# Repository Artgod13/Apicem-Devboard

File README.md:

# Description
The Apicem Devboard is a Devboard designed by me for Hack Club. Currently it uses a RP2040 MCU, USB-C Power, 16 Mb Flash Storage, Reset Button, Power Indication LED, and a Neo Pixel Status LED. The board was designed to handle 0.6 amps of power. All of these features were added with what is essential in a board in mind. This board was designed to be like a Pi-Pico but way beefier and look cooler. In theory it should be exactly the same dimensions as a Pi-Pico and it uses the same MCu as the Pi-Pico. This board is named "Apicem" as that's latin for "vertex" or "peak" showing how this board is the peak of it's kind.

## Schematic

## PCB

## 3D Images

## My Documented Journey
See [My Journal](./JOURNAL.md)

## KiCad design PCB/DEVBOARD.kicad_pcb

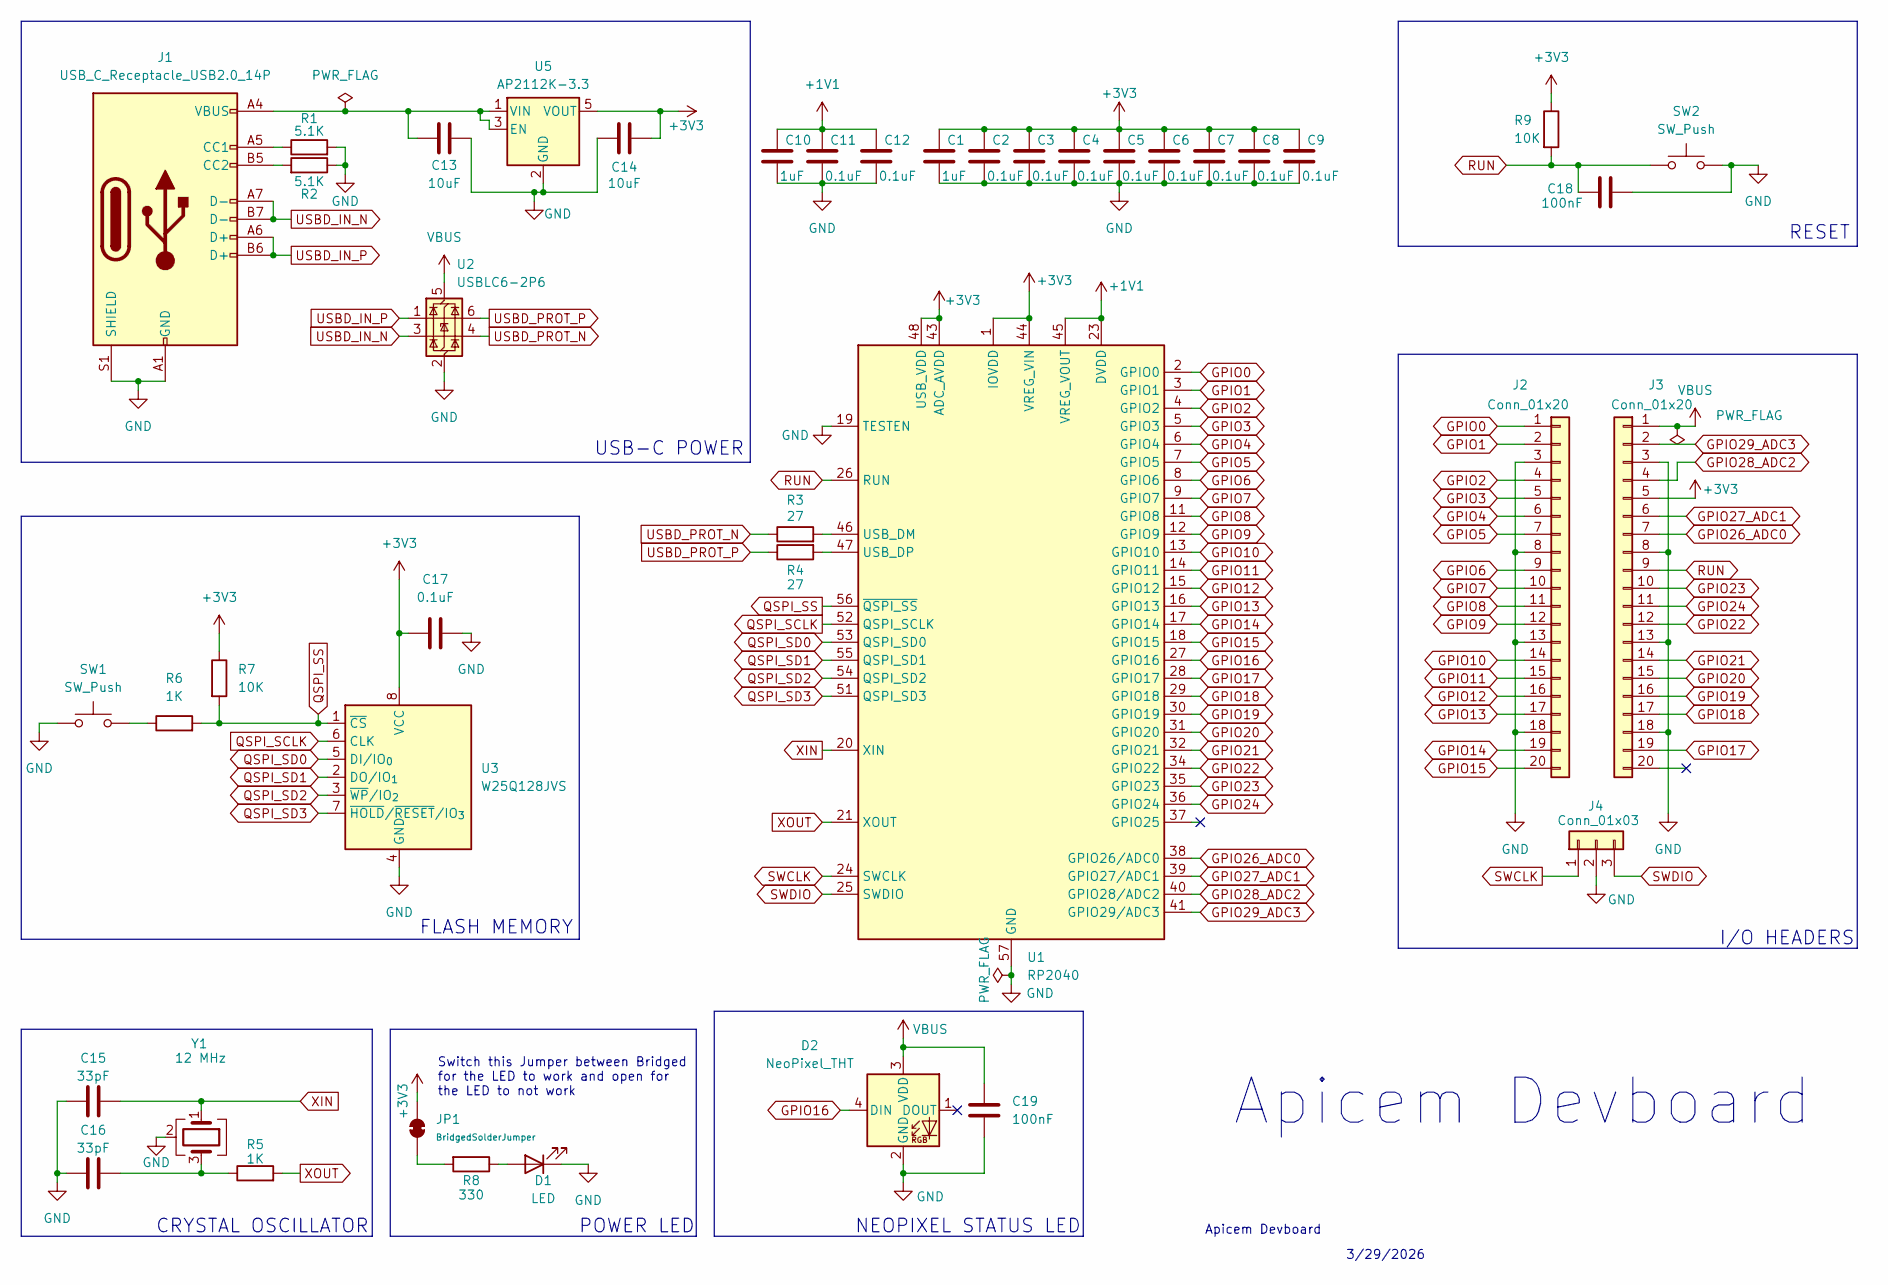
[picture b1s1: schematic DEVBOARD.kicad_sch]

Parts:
C1, C10: 1uF; C_0402_1005Metric
C2, C3, C4, C5, C6, C7, C8, C9, C11, C12, C17: 0.1uF; C_0402_1005Metric
C13, C14: 10uF; C_0603_1608Metric
C15, C16: 33pF; C_0402_1005Metric
C18, C19: 100nF; C_0402_1005Metric
D1: LED; LED_0603_1608Metric
D2: NeoPixel_THT; LED_SK6812MINI_PLCC4_3.5x3.5mm_P1.75mm
J1: USB_C_Receptacle_USB2.0_14P; USB_C_Receptacle_HRO_TYPE-C-31-M-12
J2, J3: Conn_01x20; PinHeader_1x20_P2.54mm_Vertical
J4: Conn_01x03; PinHeader_1x03_P2.54mm_Vertical
JP1: BridgedSolderJumper; SolderJumper-2_P1.3mm_Open_RoundedPad1.0x1.5mm
R1, R2: 5.1K; R_0402_1005Metric
R3, R4: 27; R_0402_1005Metric
R5, R6: 1K; R_0402_1005Metric
R7, R9: 10K; R_0402_1005Metric
R8: 330; R_0603_1608Metric
SW1, SW2: SW_Push; SW_Push_SPST_NO_Alps_SKRK
U1: RP2040; QFN-56-1EP_7x7mm_P0.4mm_EP3.2x3.2mm
U2: USBLC6-2P6; SOT-666
U3: W25Q128JVS; SOIC-8_5.3x5.3mm_P1.27mm
U5: AP2112K-3.3; SOT-23-5
Y1: 12 MHz; Crystal_SMD_3225-4Pin_3.2x2.5mm

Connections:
+1V1: C10.1, C11.1, C12.1, U1.23 (DVDD), U1.45 (VREG_VOUT), U1.50 (DVDD)
+3V3: C1.1, C2.1, C3.1, C4.1, C5.1, C6.1, C7.1, C8.1, C9.1, C14.2, C17.1, J3.5, JP1.2 (B), R7.1, R9.1, U1.1 (IOVDD), U1.10 (IOVDD), U1.22 (IOVDD), U1.33 (IOVDD), U1.42 (IOVDD), U1.43 (ADC_AVDD), U1.44 (VREG_VIN), U1.48 (USB_VDD), U1.49 (IOVDD), U3.8 (VCC), U5.5 (VOUT)
GND: C1.2, C2.2, C3.2, C4.2, C5.2, C6.2, C7.2, C8.2, C9.2, C10.2, C11.2, C12.2, C13.2, C14.1, C15.2, C16.2, C17.2, C18.2, C19.2, D1.1 (K), D2.2 (GND), J1.A1 (GND), J1.A12 (GND), J1.B1 (GND), J1.B12 (GND), J1.S1 (SHIELD), J2.3, J2.8, J2.13, J2.18, J3.3, J3.8, J3.13, J3.18, J4.2, R1.2, R2.1, SW1.1, SW2.2, U1.19 (TESTEN), U1.57 (GND), U2.2 (GND), U3.4 (GND), U5.2 (GND), Y1.2 (G), Y1.4 (G)
GPIO0: J2.1, U1.2 (GPIO0)
GPIO1: J2.2, U1.3 (GPIO1)
GPIO2: J2.4, U1.4 (GPIO2)
GPIO3: J2.5, U1.5 (GPIO3)
GPIO4: J2.6, U1.6 (GPIO4)
GPIO5: J2.7, U1.7 (GPIO5)
GPIO6: J2.9, U1.8 (GPIO6)
GPIO7: J2.10, U1.9 (GPIO7)
GPIO8: J2.11, U1.11 (GPIO8)
GPIO9: J2.12, U1.12 (GPIO9)
GPIO10: J2.14, U1.13 (GPIO10)
GPIO11: J2.15, U1.14 (GPIO11)
GPIO12: J2.16, U1.15 (GPIO12)
GPIO13: J2.17, U1.16 (GPIO13)
GPIO14: J2.19, U1.17 (GPIO14)
GPIO15: J2.20, U1.18 (GPIO15)
GPIO16: D2.4 (DIN), U1.27 (GPIO16)
GPIO17: J3.19, U1.28 (GPIO17)
GPIO18: J3.17, U1.29 (GPIO18)
GPIO19: J3.16, U1.30 (GPIO19)
GPIO20: J3.15, U1.31 (GPIO20)
GPIO21: J3.14, U1.32 (GPIO21)
GPIO22: J3.12, U1.34 (GPIO22)
GPIO23: J3.10, U1.35 (GPIO23)
GPIO24: J3.11, U1.36 (GPIO24)
GPIO26_ADC0: J3.7, U1.38 (GPIO26/ADC0)
GPIO27_ADC1: J3.6, U1.39 (GPIO27/ADC1)
GPIO28_ADC2: J3.4, U1.40 (GPIO28/ADC2)
GPIO29_ADC3: J3.2, U1.41 (GPIO29/ADC3)
unnamed: C16.1, R5.1, Y1.3
unnamed: D1.2 (A), R8.1
unnamed: J1.A5 (CC1), R1.1
unnamed: J1.B5 (CC2), R2.2
unnamed: JP1.1 (A), R8.2
unnamed: R6.1, SW1.2
unnamed: R3.2, U1.46 (USB_DM)
unnamed: R4.2, U1.47 (USB_DP)
unnamed: C13.1, J1.A4 (VBUS), J1.A9 (VBUS), J1.B4 (VBUS), J1.B9 (VBUS), U5.1 (VIN), U5.3 (EN)
QSPI_SCLK: U1.52 (QSPI_SCLK), U3.6 (CLK)
QSPI_SD0: U1.53 (QSPI_SD0), U3.5 (DI/IO_{0})
QSPI_SD1: U1.55 (QSPI_SD1), U3.2 (DO/IO_{1})
QSPI_SD2: U1.54 (QSPI_SD2), U3.3 (~WP/IO_{2})
QSPI_SD3: U1.51 (QSPI_SD3), U3.7 (~HOLD/~RESET/IO_{3})
QSPI_SS: R6.2, R7.2, U1.56 (~QSPI_SS), U3.1 (~CS)
RUN: C18.1, J3.9, R9.2, SW2.1, U1.26 (RUN)
SWCLK: J4.1, U1.24 (SWCLK)
SWDIO: J4.3, U1.25 (SWDIO)
USBD_IN_N: J1.A7 (D-), J1.B7 (D-), U2.3 (I/O2)
USBD_IN_P: J1.A6 (D+), J1.B6 (D+), U2.1 (I/O1)
USBD_PROT_N: R3.1, U2.4 (I/O2)
USBD_PROT_P: R4.1, U2.6 (I/O1)
VBUS: C19.1, D2.3 (VDD), J3.1, U2.5 (VBUS)
XIN: C15.1, U1.20 (XIN), Y1.1
XOUT: R5.2, U1.21 (XOUT)

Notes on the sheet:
Apicem Devboard
3/29/2026
I/O HEADERS
USB-C POWER
CRYSTAL OSCILLATOR
POWER LED
NEOPIXEL STATUS LED
FLASH MEMORY
Switch this Jumper between Bridged for the LED to work and open for the LED to not work
RESET

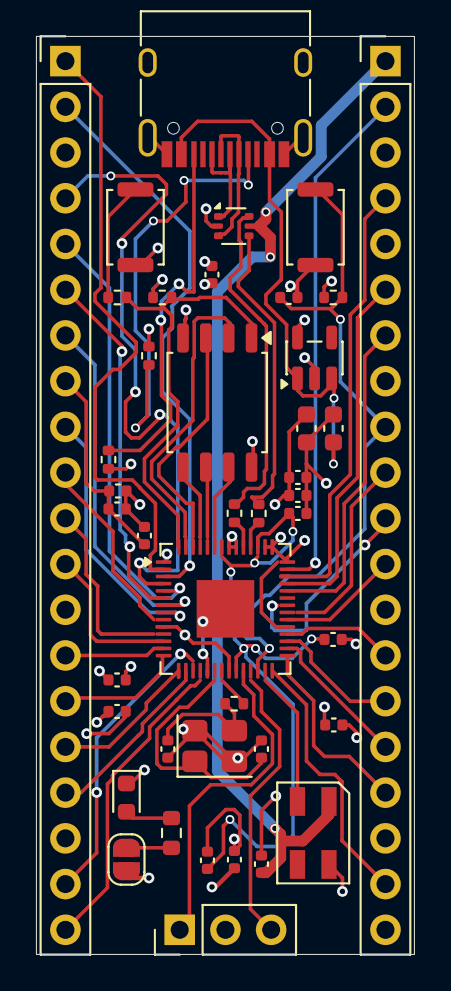
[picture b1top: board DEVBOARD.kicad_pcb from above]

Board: 4 copper layers, 21.0 x 51.0 mm, 42 parts (0 on the bottom side), 57 nets.

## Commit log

2026-03-30 Rename project to Apicem Devboard
    Updated project name and description in README.
2026-03-30 Create a
2026-03-30 Update README with project logo and description
    Added project logo to README and expanded project description.
2026-03-30 Fix image syntax in README.md
2026-03-30 Update README to remove logo and enhance description
    Removed logo image reference and updated project description.
2026-03-30 Change image link to Apicem cover art
    Updated image link in README to point to cover art.
2026-03-30 Remove cover art link from README
    Removed the cover art link from the README.
2026-03-30 Add project logo to README
    Added project logo to README.
2026-03-30 Enhance README title formatting
    Updated project title formatting and emphasized it with bold.
2026-04-03 Add PCB images to README
    Added PCB images to the README file.
2026-04-03 Add 3D Images section to README
    Added section for 3D Images with additional images.
2026-04-03 Replace 3D image in README with a new image
2026-04-03 Add documented journey section to README
    Added a section for documenting the journey and linked to the journal.
2026-04-03 Re-add 'My Documented Journey' section to README
2026-04-03 Create IMAGES
